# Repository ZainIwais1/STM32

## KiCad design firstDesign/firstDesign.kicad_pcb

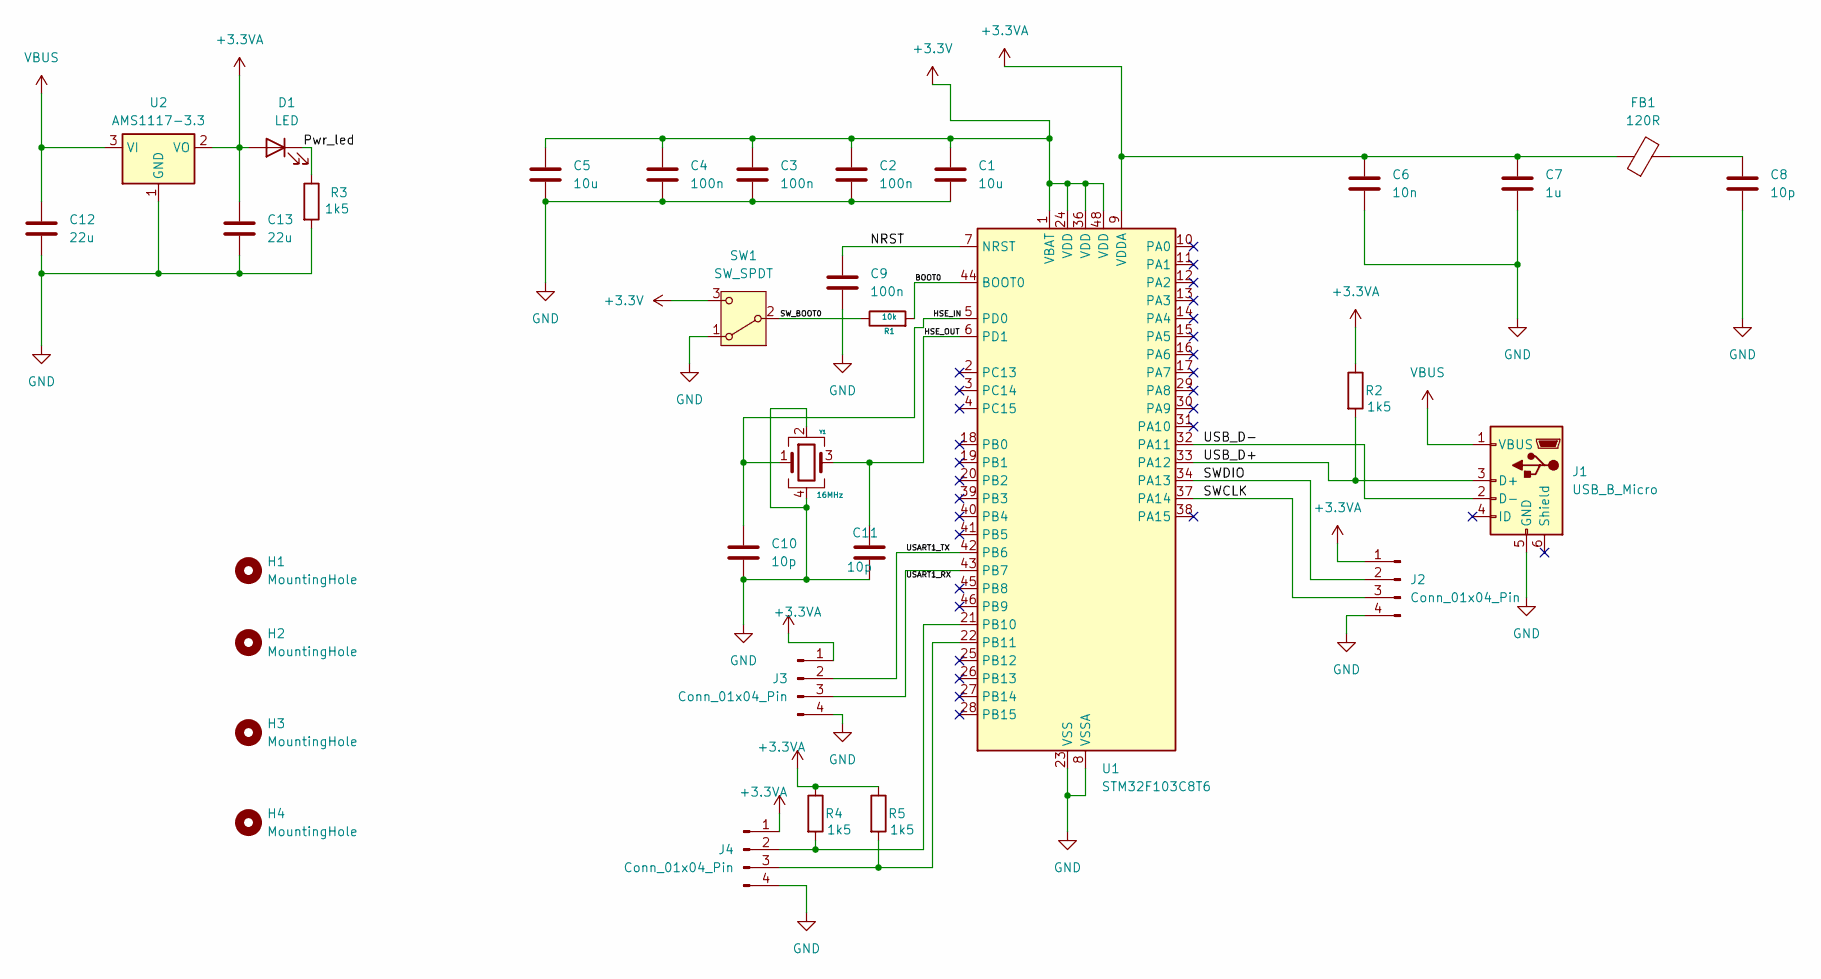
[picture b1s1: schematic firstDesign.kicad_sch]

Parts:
C1: 10u; C_0402_1005Metric
C2, C3, C4, C9: 100n; C_0402_1005Metric
C5: 10u; C_0805_2012Metric
C6: 10n; C_0402_1005Metric
C7: 1u; C_0402_1005Metric
C8, C10, C11: 10p; C_0402_1005Metric
C12, C13: 22u; C_0805_2012Metric
D1: LED; LED_0603_1608Metric
FB1: 120R; L_0603_1608Metric_Pad1.05x0.95mm_HandSolder
H1, H2, H3, H4: MountingHole; MountingHole_2.2mm_M2
J1: USB_B_Micro; USB_Micro-B_Wuerth_629105150521
J2, J3, J4: Conn_01x04_Pin; PinHeader_1x04_P2.54mm_Vertical
R1: 10k; R_0402_1005Metric
R2, R3, R4, R5: 1k5; R_0402_1005Metric
SW1: SW_SPDT; SW_SPDT_PCM12
U1: STM32F103C8T6; LQFP-48_7x7mm_P0.5mm
U2: AMS1117-3.3; SOT-223-3_TabPin2
Y1: 16MHz; Crystal_SMD_3225-4Pin_3.2x2.5mm

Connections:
+3.3V: C1.1, C2.1, C3.1, C4.1, C5.1, SW1.3 (C), U1.1 (VBAT), U1.24 (VDD), U1.36 (VDD), U1.48 (VDD)
+3.3VA: C6.1, C7.1, C13.1, D1.2 (A), FB1.1, J2.1, J3.1, J4.1, R2.1, R4.1, R5.1, U1.9 (VDDA), U2.2 (VO)
/BOOT0: R1.2, U1.44 (BOOT0)
/HSE_IN: C10.1, U1.5 (PD0), Y1.1
/HSE_OUT: C11.1, U1.6 (PD1), Y1.3
/NRST: C9.1, U1.7 (NRST)
/Pwr_led: D1.1 (K), R3.1
/SWCLK: J2.3, U1.37 (PA14)
/SWDIO: J2.2, U1.34 (PA13)
/SW_BOOT0: R1.1, SW1.2 (B)
/USART1_RX: J3.3, U1.43 (PB7)
/USART1_TX: J3.2, U1.42 (PB6)
/USB_D+: J1.3 (D+), R2.2, U1.33 (PA12)
/USB_D-: J1.2 (D-), U1.32 (PA11)
GND: C1.2, C2.2, C3.2, C4.2, C5.2, C6.2, C7.2, C8.2, C9.2, C10.2, C11.2, C12.2, C13.2, J1.5 (GND), J2.4, J3.4, J4.4, R3.2, SW1.1 (A), U1.8 (VSSA), U1.23 (VSS), U1.35 (VSS), U1.47 (VSS), U2.1 (GND), Y1.2, Y1.4
unnamed: C8.1, FB1.2
unnamed: J4.2, R4.2, U1.21 (PB10)
unnamed: J4.3, R5.2, U1.22 (PB11)
VBUS: C12.1, J1.1 (VBUS), U2.3 (VI)

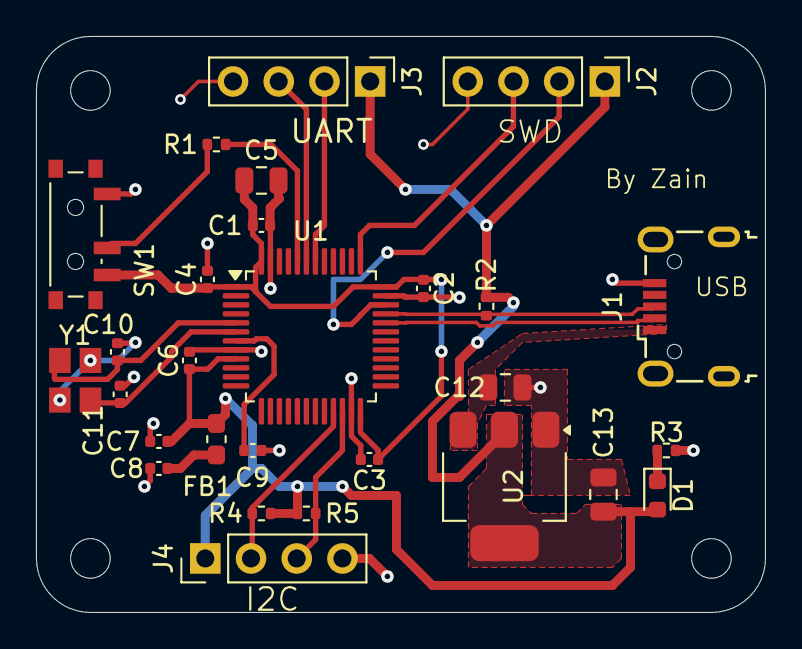
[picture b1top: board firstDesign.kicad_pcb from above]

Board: 2 copper layers, 40.5 x 32.0 mm, 32 parts (0 on the bottom side), 19 nets.

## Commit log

2024-08-18 PCB For STM
